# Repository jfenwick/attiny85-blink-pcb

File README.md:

# attiny85-blink-pcb

PCB with an ATtiny85 that blinks an LED, with an ISP jumper for programming using a USBTinyISP or clone programmer.

<br>
PCB in KiCAD.

<br>
3D rendering from KiCAD.

<br>
3D rendering imported to Solidworks using FreeCAD StepUp plugin.

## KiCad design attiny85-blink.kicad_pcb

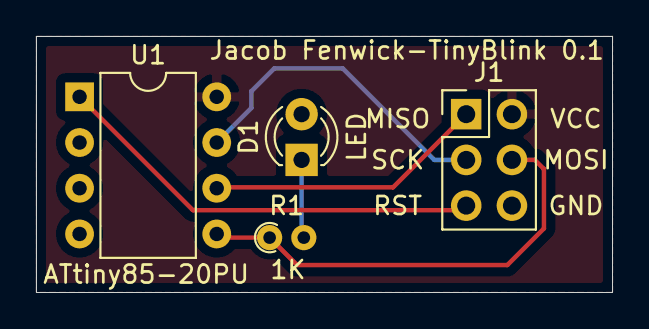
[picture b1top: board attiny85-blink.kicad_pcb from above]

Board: 2 copper layers, 32.0 x 14.2 mm, 4 parts (0 on the bottom side), 7 nets.

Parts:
D1: LED; LED_D3.0mm
J1: AVR-ISP-6; PinHeader_2x03_P2.54mm_Vertical
R1: 1K; R_Axial_DIN0204_L3.6mm_D1.6mm_P1.90mm_Vertical
U1: ATtiny85-20PU; DIP-8_W7.62mm

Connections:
GND: D1.2, J1.6, U1.4
unnamed: D1.1, R1.2
unnamed: J1.1, U1.6
unnamed: J1.3, U1.7
unnamed: J1.4, R1.1, U1.5
unnamed: J1.5, U1.1
VCC: J1.2, U1.8

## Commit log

2021-04-13 Added pcb files
2021-04-24 Added VCC and GND to schematic, moved around traces and made copper pours on PCB.
